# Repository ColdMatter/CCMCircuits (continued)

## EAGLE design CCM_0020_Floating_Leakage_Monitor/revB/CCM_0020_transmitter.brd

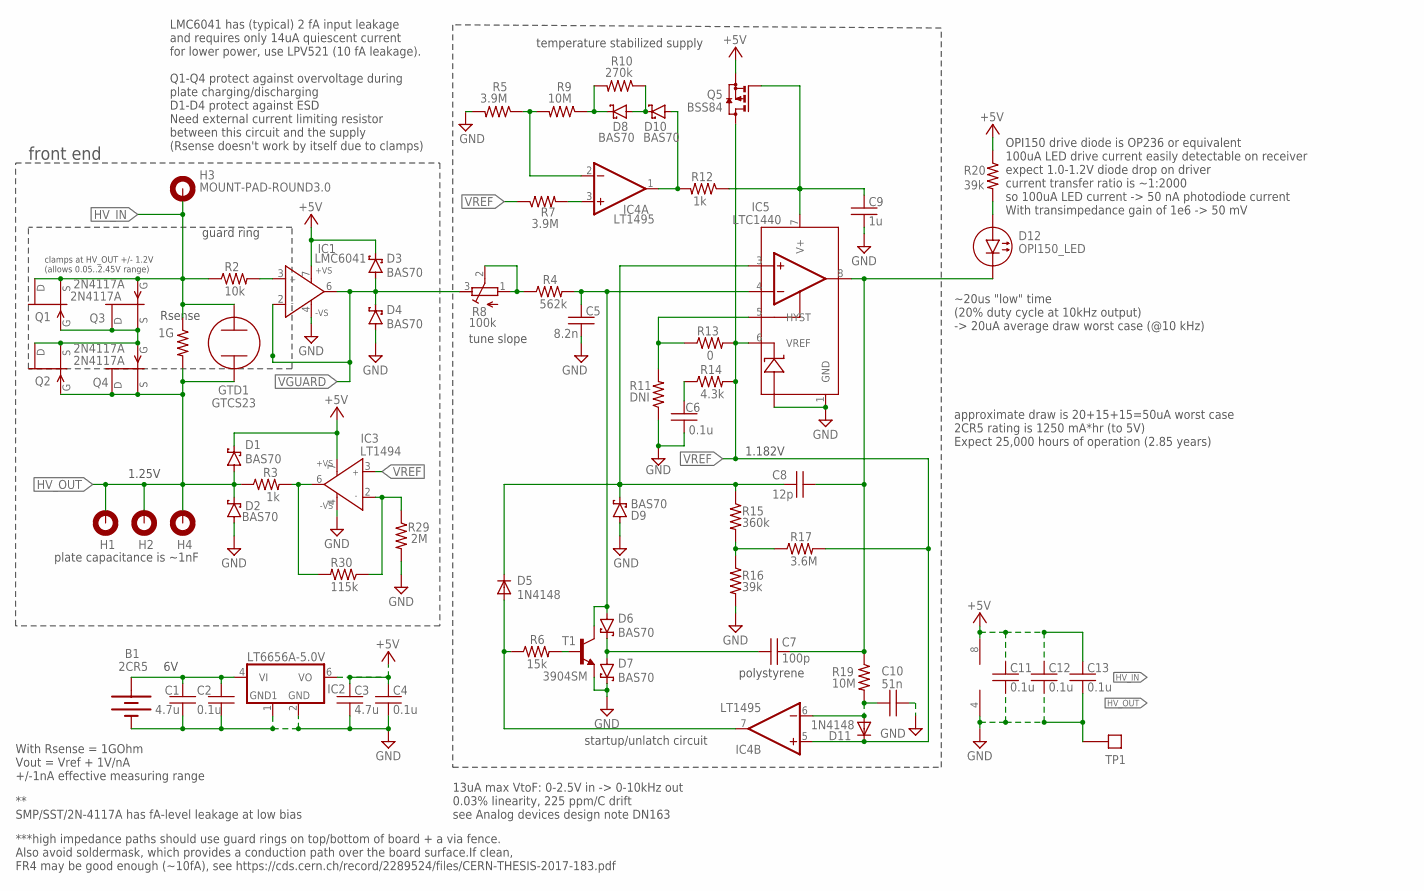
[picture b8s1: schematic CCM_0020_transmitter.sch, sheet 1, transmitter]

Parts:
B1: 2CR5
C1, C3: 4.7u; 0603
C2, C4, C6, C11, C12, C13: 0.1u; 0603
C5: 8.2n; 0603
C7: 100p; 0603
C8: 12p; 0603
C9: 1u; 0603
C10: 51n; 0603
D1, D2, D3, D4, D6, D7, D8, D9, D10: BAS70; SOT23
D5, D11: 1N4148; SOD323_ST
D12: OPI150_LED
GTD1: GTCS23
H1, H2, H3, H4: MOUNT-PAD-ROUND3.0; 3,0-PAD
IC1: LMC6041; SO08
IC2: LT6656A-5.0V; SOT23-6
IC3: LT1494; SO08
IC4: LT1495; SO08
IC5: LTC1440; SO8
Q1, Q2, Q3, Q4: 2N4117A; SOT23
Q5: BSS84; SOT23
R1: 1G; 2512
R2: 10k; 0603
R3, R12: 1k; 0603
R4: 562k; 0603
R5, R7: 3.9M; 0603
R6: 15k; 0603
R8: 100k; RTRIM3224W
R9, R19: 10M; 0603
R10: 270k; 0603
R11: DNI; 0603
R13: 0; 0603
R14: 4.3k; 0603
R15: 360k; 0603
R16, R20: 39k; 0603
R17: 3.6M; 0603
R29: 2M; 0603
R30: 115k; 0603
T1: 3904SM; SOT23
TP1: TESTPOINT

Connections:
+5V: C3.1, C4.1, C11.1, C12.1, C13.1, D1.3 (C), D3.3 (C), IC1.7 (+VS), IC2.6 (VO), IC3.7 (+VS), IC4.8 (V+), Q5.2 (S), R20.1
GND: B1.V- (-), C1.2, C2.2, C3.2, C4.2, C5.2, C6.1, C9.2, C10.2, C11.2, C12.2, C13.2, D2.1 (A), D4.1 (A), D7.3 (C), D9.1 (A), IC1.4 (-VS), IC2.1 (GND1), IC2.2 (GND), IC3.4 (-VS), IC4.4 (V-), IC5.1 (GND), IC5.2 (V-), R5.2, R11.1, R16.2, R29.2, T1.2 (E), TP1.P$1
HV_IN: GTD1.P$1 (1), H3.B3,0, Q1.1 (D), Q1.2 (S), Q3.3 (G), R1.1, R2.1
HV_IN1: Q1.3 (G), Q2.1 (D), Q2.2 (S), Q3.1 (D), Q3.2 (S), Q4.3 (G)
HV_OUT: D1.1 (A), D2.3 (C), GTD1.P$2 (2), H1.B3,0, H2.B3,0, H4.B3,0, Q2.3 (G), Q4.1 (D), Q4.2 (S), R1.2, R3.1
HYST: IC5.5 (HYST), R11.2, R13.1
unnamed: C9.1, IC5.7 (V+), Q5.1 (G), R12.1
unnamed: D12.P$1 (1(A)), R20.2
unnamed: R4.1, R8.1 (A), R8.2 (S)
unnamed: IC1.3 (IN+), R2.2
unnamed: C6.2, R14.1
unnamed: C5.1, D6.1 (A), IC5.4 (-IN), R4.2, T1.3 (C)
unnamed: C7.1, D6.3 (C), D7.1 (A)
unnamed: R6.2, T1.1 (B)
unnamed: D5.A, IC4.7 (OUT), R6.1
unnamed: R15.2, R16.1, R17.1
unnamed: C8.1, D5.C, D9.3 (C), IC5.3 (+IN), R15.1
unnamed: C10.1, D11.A, IC4.6 (-IN), R19.2
unnamed: D8.1 (A), D10.3 (C), R10.1
unnamed: D8.3 (C), R9.1, R10.2
unnamed: IC4.2 (-IN), R5.1, R9.2
unnamed: B1.V+ (+), C1.1, C2.1, IC2.4 (VI)
unnamed: D10.1 (A), IC4.1 (OUT), R12.2
unnamed: IC4.3 (+IN), R7.2
unnamed: IC3.2 (IN-), R29.1, R30.1
unnamed: IC3.6 (OUT), R3.2, R30.2
VGUARD: D3.1 (A), D4.3 (C), IC1.2 (IN-), IC1.6 (OUT), R8.3 (E)
VREF: D11.C, IC3.3 (IN+), IC4.5 (+IN), IC5.6 (VREF), Q5.3 (D), R7.1, R13.2, R14.2, R17.2
VTOF_OUTPUT: C7.2, C8.2, D12.P$2 (2(C)), IC5.8 (OUT), R19.1

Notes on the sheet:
** SMP/SST/2N-4117A has fA-level leakage at low bias
plate capacitance is ~1nF
With Rsense = 1GOhm Vout = Vref + 1V/nA +/-1nA effective measuring range
***high impedance paths should use guard rings on top/bottom of board + a via fence. Also avoid soldermask, which provides a conduction path over the board surface.If clean, FR4 may be good enough (~10fA), see https://cds.cern.ch/record/2289524/files/CERN-THESIS-2017-183.pdf
polystyrene
front end
13uA max VtoF: 0-2.5V in -> 0-10kHz out 0.03% linearity, 225 ppm/C drift see Analog devices design note DN163
1.182V
clamps at HV_OUT +/- 1.2V (allows 0.05..2.45V range)
approximate draw is 20+15+15=50uA worst case 2CR5 rating is 1250 mA*hr (to 5V) Expect 25,000 hours of operation (2.85 years)
guard ring
~20us "low" time (20% duty cycle at 10kHz output) -> 20uA average draw worst case (@10 kHz)
OPI150 drive diode is OP236 or equivalent 100uA LED drive current easily detectable on receiver expect 1.0-1.2V diode drop on driver current transfer ratio is ~1:2000 so 100uA LED current -> 50 nA photodiode current With transimpedance gain of 1e6 -> 50 mV
LMC6041 has (typical) 2 fA input leakage and requires only 14uA quiescent current for lower power, use LPV521 (10 fA leakage). Q1-Q4 protect against overvoltage during plate charging/discharging D1-D4 protect against ESD Need external current limiting resistor between this circuit and the supply (R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
Rsense
temperature stabilized supply
startup/unlatch circuit
tune slope
1.25V

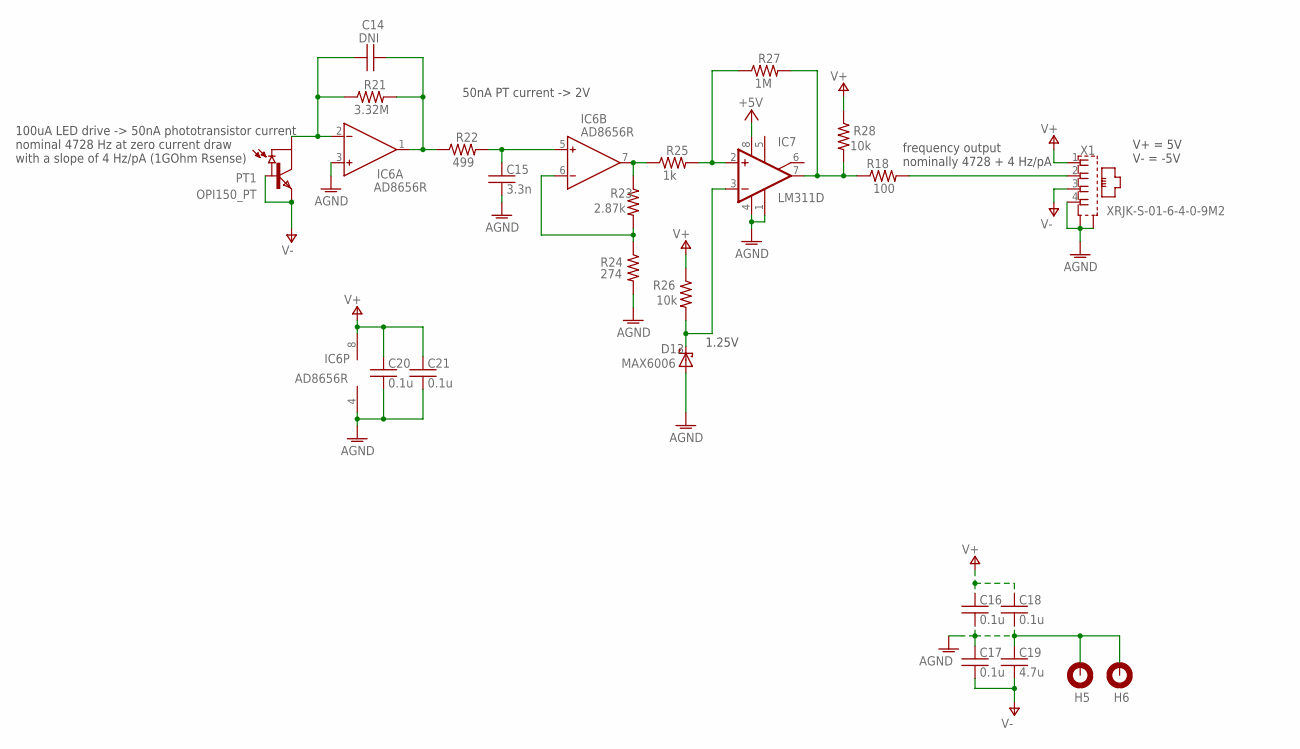
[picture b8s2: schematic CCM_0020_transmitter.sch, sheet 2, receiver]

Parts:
C14: DNI; 0603
C15: 3.3n; 0603
C16, C17, C18, C20, C21: 0.1u; 0603
C19: 4.7u; 0603
D13: MAX6006; SOT23
H5, H6: MOUNT-PAD-ROUND3.0; 3,0-PAD
IC6: AD8656R; SO8
IC7: LM311D; SO08
PT1: OPI150_PT; OPI150_PHOTOTRANSISTOR
R18: 100; 0603
R21: 3.32M; 0603
R22: 499; 0603
R23: 2.87k; 0603
R24: 274; 0603
R25: 1k; 0603
R26, R28: 10k; 0603
R27: 1M; 0603
X1: XRJK-S-01-6-4-0-9M2

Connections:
AGND: C15.2, C16.2, C17.1, C18.2, C19.1, C20.2, C21.2, D13.2 (A), H5.B3,0, H6.B3,0, IC6.3 (IN+), IC6.4 (V-), IC7.1 (GND), IC7.4 (V-), R24.2, X1.4, X1.S1 (S), X1.S2 (S)
FOUT: IC7.7 (OUT), R18.1, R27.2, R28.2
unnamed: R18.2, X1.2
unnamed: C14.1, IC6.2 (IN-), PT1.P3 (COLLECTOR), R21.1
unnamed: C14.2, IC6.1 (OUT), R21.2, R22.1
unnamed: C15.1, IC6.5 (IN+), R22.2
unnamed: IC6.6 (IN-), R23.2, R24.1
unnamed: IC6.7 (OUT), R23.1, R25.1
unnamed: IC7.2 (+IN), R25.2, R27.1
unnamed: D13.1 (C), IC7.3 (-IN), R26.2
V+: C16.1, C18.1, C20.1, C21.1, IC6.8 (V+), IC7.8 (V+), R26.1, R28.1, X1.1
V-: C17.2, C19.2, PT1.P4 (BASE), PT1.P5 (EMITTER), X1.3

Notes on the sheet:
100uA LED drive -> 50nA phototransistor current nominal 4728 Hz at zero current draw with a slope of 4 Hz/pA (1GOhm Rsense)
50nA PT current -> 2V
1.25V
frequency output nominally 4728 + 4 Hz/pA
V+ = 5V V- = -5V

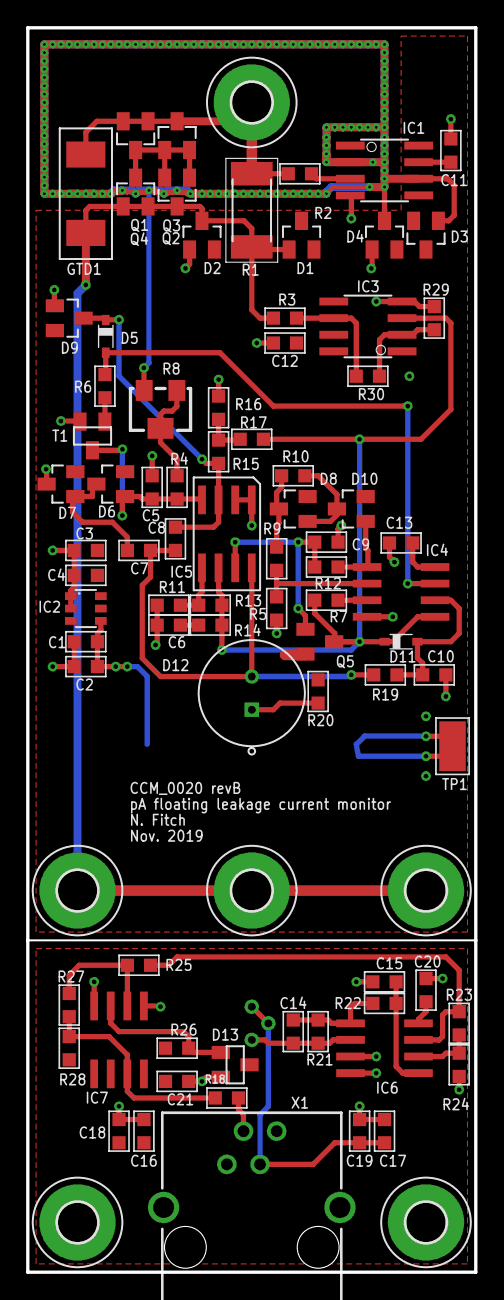
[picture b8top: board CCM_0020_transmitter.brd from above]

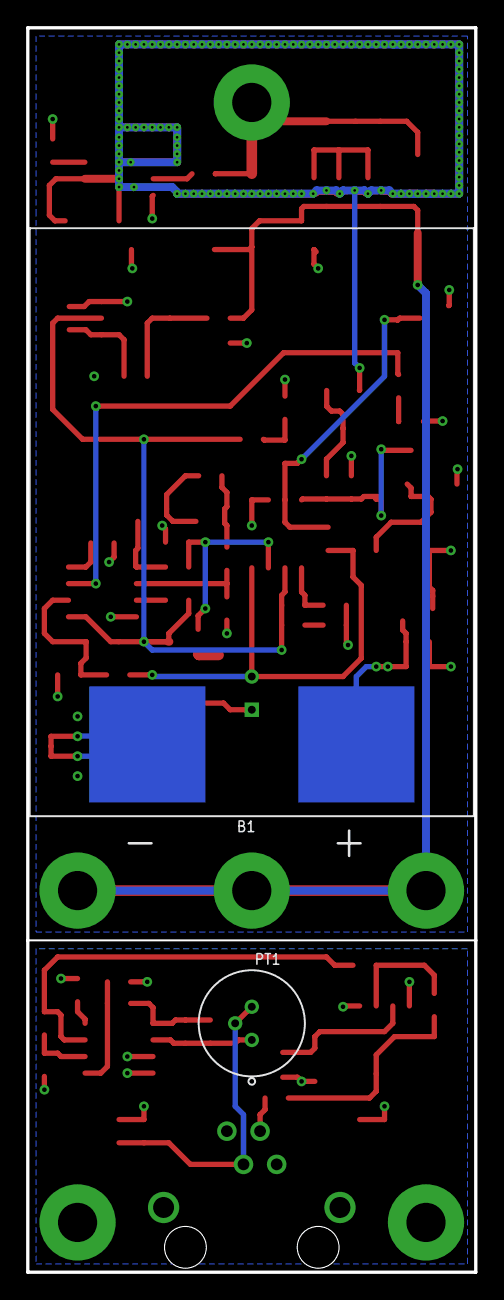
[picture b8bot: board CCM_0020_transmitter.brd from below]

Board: 2 copper layers, 34.3 x 95.2 mm, 88 parts (2 on the bottom side), 41 nets.

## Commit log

2014-03-31 Add Photodiode Amplifier
    This is a photodiode amplifier circuit with about 50kHz bandwidth useful
    for transfer cavity or power monitoring.
2014-03-31 Add Diode Noise stabilisation circuit
    Add my work in progress circuit to stabilise the noise on a diode laser,
    some more details of the circuit can be found in the "About" document.
2014-04-01 Add Ben's VCO
    This is the standard VCO circuit with an MAT-3 attenuator
2014-04-02 Use readme.md instead of About.txt.
    Easier to browse on GitHub.
2014-04-04 Insert 50 ohm resistor into output
    This actually makes the circuit work properly, previously I was doing this
    with a terminator, but that's a bit dangerous for your ICS
2014-04-14 April 2014 VCO modification
    The proper files for my VCO
2014-04-14 Pictures of a slightly older version of circuit
    To get orientation of chokes and amplifiers.
2014-06-01 Add a 50Hz function generator circuit
2014-06-01 Some changes to make the function generator board work
2014-06-02 finished version of the board
2014-06-03 Add a microwave transmission line board at 14.5GHz
2014-06-03 Include boadmaster files for 50Hz FGen
2014-06-05 add Longer board
2014-06-08 New board with taper section
2014-06-08 A few changes to microwave boards
2014-06-18 Update to VCO
    I updated the production files, though I didn't see anything wrong with
    them on my computer. It might be an Eagle version problem, so I suggest
    using the .sol .cmp etc directly.
2014-07-14 New version of the diode stabliser circuit
2014-09-02 Various new circuits
    Fast photodiode amp
    200V piezo driver
2015-11-23 adding some circuits to the repo
2015-12-17 fixed stepper motor firmware bug with parameter saving (v1.5)
2015-12-17 removing massive stepper motor GUI (full) installer, the partial one should be sufficient
2016-01-11 completed design of CCM_0006 (magnetic field measuring pickup coil)
2016-01-13 added resources for updating the firmware of the reflow oven
2016-01-13 added documentation for charging LiIon batteries for CCM_0006
2016-01-21 added wonderful/horrible user manual for the reflow oven (an epic example of poor chinese-to-english translation)
2016-01-21 cleaning up inadvertant submodule creation when renaming a folder
2016-01-21 adding back folder for reflow oven
2016-01-21 added some more reflow oven documents
2016-02-19 Some notes on the commercial VCO board
    The particular problem is that the amplitude adjust driver didn't work. The notes explain a workaround.
2016-04-27 PeizoAmp
    This is the version that was submitted to DirtyPCBs (although that version had a 0 isolate on the top layer, which I fixed here).
2016-04-27 Added files via upload
    This is the circuit that was sent to DirtyPCBs
2016-04-27 A mistake
2016-04-27 Trying to clean up
    Clean up, add Piezo sent to DirtyPCB
2016-04-27 More cleaning up
    Also added updated library
2017-02-03 some minor updates
2017-02-03 Added materials for microphone-based cryocooler phase locker.
2017-02-03 CCM_0007: finished initial board layout.
2017-02-07 More work on cryocooler interlock, uploaded ordering files.
2017-03-15 Ben adding FET driver and other bits
2017-04-05 updates to custom parts library
2017-04-10 updating custom parts and FET driver
2017-04-21 started work on new coil driver
2017-05-02 Finished coil driver controller.
2017-05-10 Added CAD and docs for CCM_0008
2017-06-26 CCM_0008: added front panel and started output stage design
2017-07-05 Changes to cryocooler phaselock
2017-07-05 added MPPC parts to custum parts lbr
2017-08-01 CCM_0008: fixed current monitor schematic wiring error, prototype run current-monitor output will rail if not fixed in hardware.
2017-08-01 CCM_0008: added preliminary output stage design
2017-08-09 CCM_0007: finished schematic design of v2.
2017-08-14 CCM_0007: finished layout of v2.
2017-08-14 CCM_0007 v2: added production files and quotation
2017-08-18 Added CCM_0009: 3-channel precision bipolar current driver.
2017-09-05 update to include MPPC files, mainly
2017-09-29 Added docs for floating H-bridge (CCM_0009)
2017-09-29 Renamed folder to avoid confusion
2017-10-02 production files for CCM_0009
2017-10-02 renaming CCM_0010 docs
2017-10-02 Initial schematic design of floating H-bridge driver (CCM_0010)
2017-10-11 Added production files for CCM_0010
2017-10-26 updated custum.lbr, add a few projects
2017-10-30 CCM_0010: component value updates
2018-02-01 started design of hardware TCL
2018-03-19 Added subrack backplane board, which defines a bus standard for circuits moving forward.
2018-04-25 Added production materials for subrack backplane (0011).
2018-05-01 Added preliminary materials for subrack power and HTCL
2018-05-22 Added laser diode protection circuit
2018-05-22 Fixed circuit number conflict~
2018-09-06 Shutter driver added.
2018-09-19 Added IXFN FET connector board and revB of floating H-bridge driver.
2018-10-25 Finalized design of revB of CCM_0010. Floating H-bridge now uses a lower power driver, makes it possible to monitor the coil current, and implements an optically isolated bypass option. This latter f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
2019-02-01 New leakage monitor files
2019-03-11 Updated designs for MOT coil control and H-bridge switching
2019-06-13 Updated component values on circuits used for MOT coil driving and H-bridges.
2019-06-13 Added preliminary description of floating pA leakage monitor.
2019-08-06 Added preliminary designs of CCM_0020, a floating pA leakage current monitor for the new ultracold edm electric-field plates.
2019-08-06 Added directories with design resources and descriptions of our all singing all dancing MOT coil control circuits built using CCM_0008 and CCM_0010.
2019-08-06 library update and preliminary design of coil protection circuit
2019-08-09 Simplified leakage monitor receiver.
2019-08-21 CCM_0020 directory organization
2020-02-03 many changes
2020-02-05 updates to schematic of CCM_0025, PID
2020-02-10 Finished layout design of CCM_0020_revC
